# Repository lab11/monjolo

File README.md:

Monjolo
=======

Monjolo sensors are designed to meter energy consumers, such as plug loads,
lighting, water heaters, etc. Monjolo exploits an interesting fact to accomplish
this: energy consuming loads (e.g. overhead lighting) often produce side
channels of energy that can be harvested (e.g. light with a solar panel).
Monjolo nodes use an energy-harvesting power supply to scavenge energy from
these side channels to power themselves. The sensors then infer information
about the original load based on the rate it is able to harvest. Monjolo nodes
follow a simple principle: the faster the rate of harvesting the greater the
amount of energy consumed by the monitored load.

The operation of a Monjolo node proceeds as follows: the harvester charges
a capacitor to some threshold. Once the threshold is met, the processing
core of the node activates and transmits a packet. The capacitor is then
drained to a lower threshold where the processing core is disabled and
the recharging process recommences. A central receiver collects all of these
packets and calculates the activation rate of the Monjolo node. This rate
is then used to meter the energy consumer.

This differs from traditional sensing because there is no explicit sensor
on the device. The sensing apparatus is entirely composed of the
energy-harvester and the packet receiver. All information is contained in
the rate of activations of the Monjolo node.

We have developed Three instantiations of this metering design. First is
Coilcube, a power meter for AC loads. Second is a light sensor for metering
lighting. And third is a thermoelectric design for metering temperature
differential.

Coilcube
--------

[

](https://raw.github.com/lab11/monjolo/master/media/coilcube_case.jpg)
[

](https://raw.github.com/lab11/monjolo/master/media/coilcube_open.jpg)

Coilcube is an AC power meter that comes in two forms: plug-load and split-core.

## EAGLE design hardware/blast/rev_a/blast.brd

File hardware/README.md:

Hardware (PCBs)
===============

This folder contains hardware for the various Monjolo nodes.

| Board                 | Folder             | Description                                                                |
|-----------------------|--------------------|----------------------------------------------------------------------------|
| Coilcube Power Supply | cc_power_supply    | An AC current transformer based energy-harvesting power supply.            |
| Coilcube              | coilcube           | Plug load AC meter. Contains processing core.                              |
| Gecko Power Supply    | gecko_power_supply | Energy-harvesting power supply for solar cell.                             |
| Impulse               | impulse            | Processing core. Contains, uC, radio, antenna, FRAM, and timing capacitor. |
| sEHnsor               | sEHnsor            | Processing core like Impulse based on the CC2538.                          |

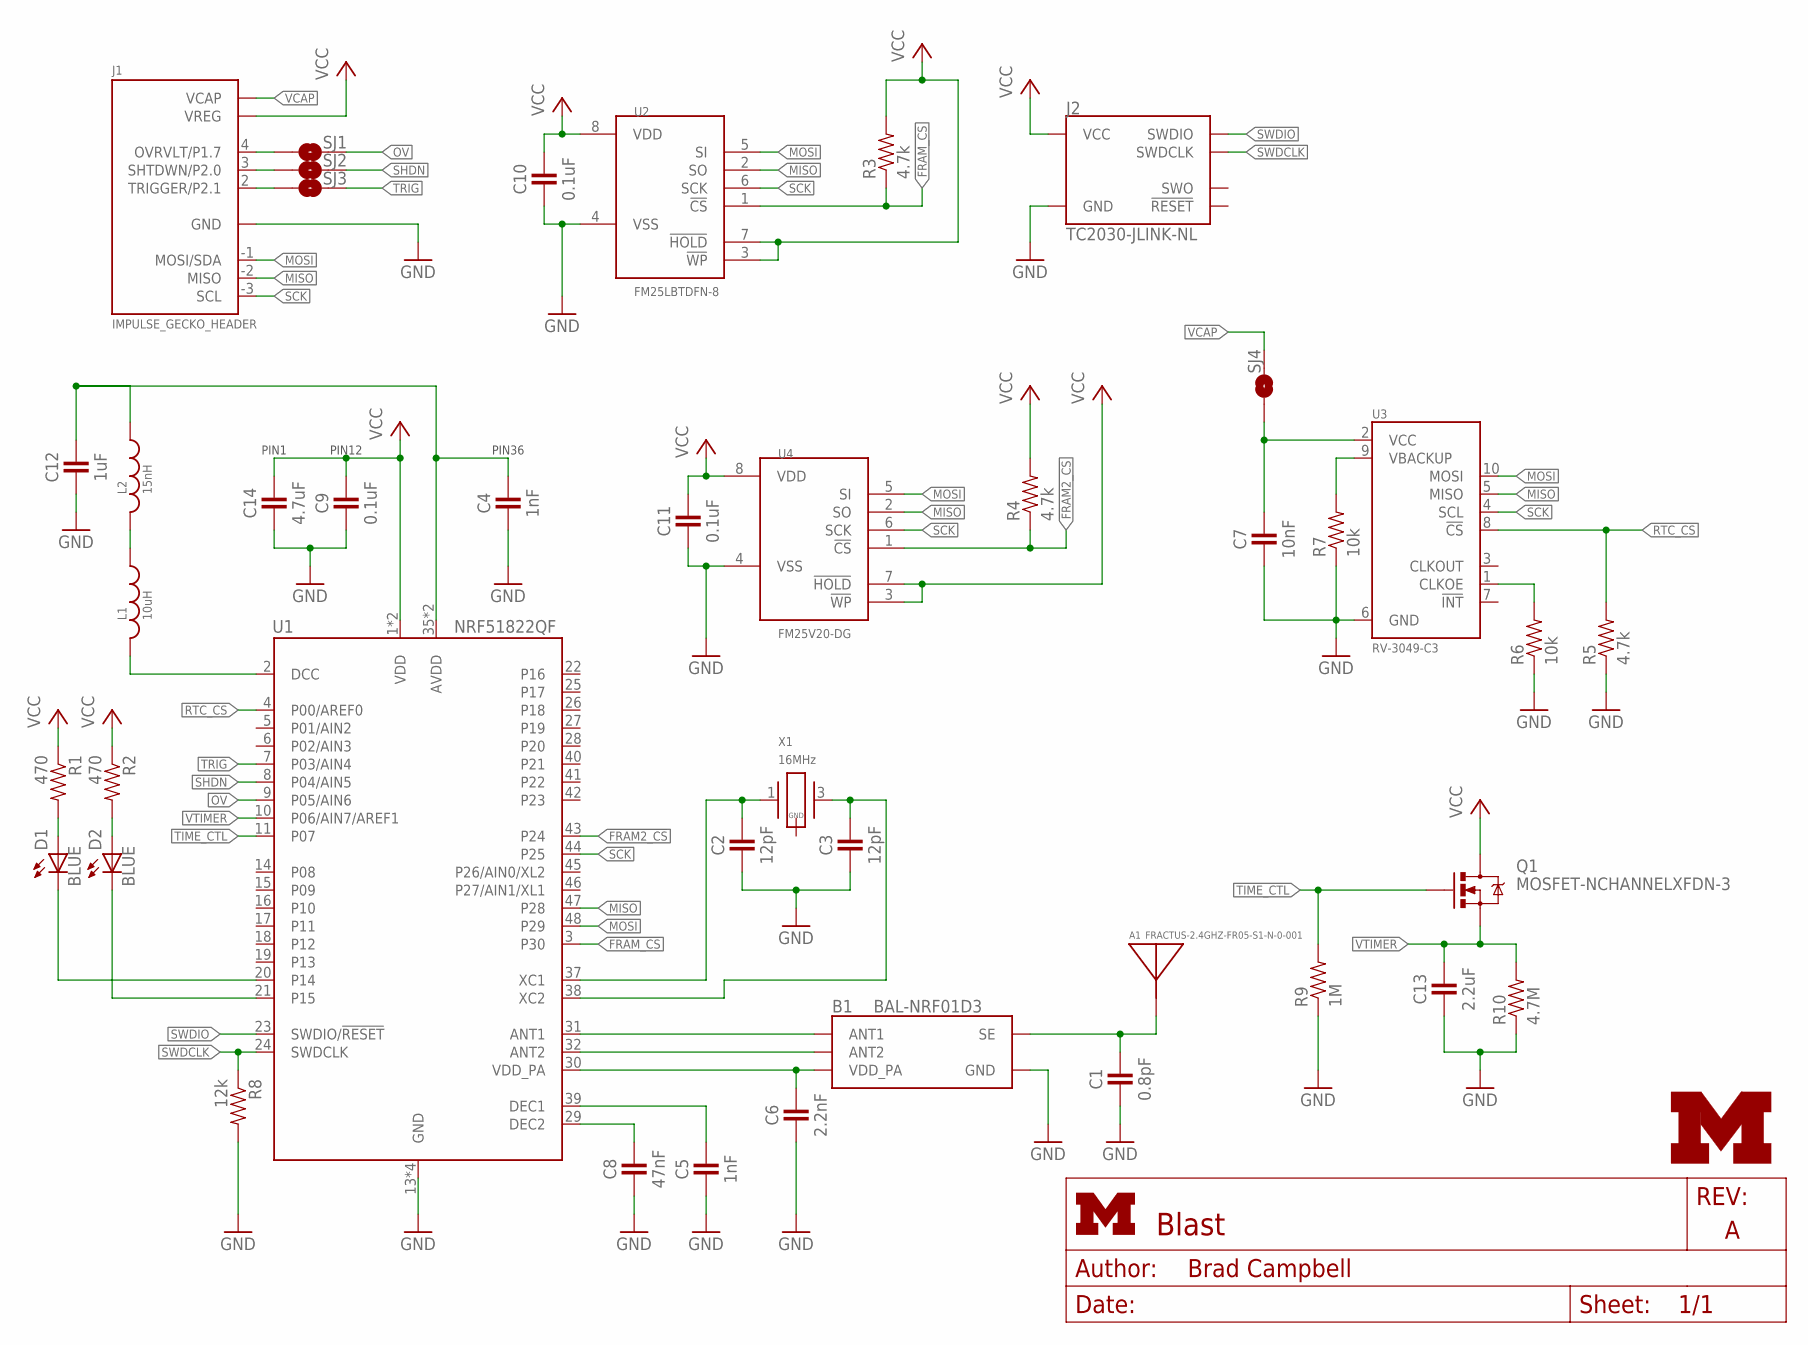
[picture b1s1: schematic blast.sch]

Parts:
A1: FRACTUS-2.4GHZ-FR05-S1-N-0-001; FRACTUS-ANTENNA-FR05-S1-N-0-001
B1: BAL-NRF01D3
C1: 0.8pF; 0402_CAP; DIGIKEY 490-6269-1-ND
C2, C3: 12pF; 0402_CAP; DIGIKEY 490-6197-1-ND
C4, C5: 1nF; 0402_CAP; DIGIKEY 490-1303-1-ND
C6: 2.2nF; 0402_CAP; DIGIKEY 490-5419-1-ND
C7: 10nF; 0402_CAP; DIGIKEY 445-1260-1-ND
C8: 47nF; 0402_CAP; DIGIKEY 445-1264-1-ND
C9, C10, C11: 0.1uF; 0402_CAP; DIGIKEY 445-4952-1-ND
C12: 1uF; 0402_CAP; DIGIKEY 1276-1513-1-ND
C13: 2.2uF; 0402_CAP; DIGIKEY 445-3882-1-ND
C14: 4.7uF; 0402_CAP; DIGIKEY 445-5947-1-ND
D1, D2: BLUE; LED-0603; DIGIKEY 160-1837-1-ND
J1: IMPULSE_GECKO_HEADER; HEADER1X9/0.05IN
J2: TC2030-JLINK-NL; TC2030-IDC-NL
L1: 10uH; 0603_CAP; DIGIKEY 490-4025-1-ND
L2: 15nH; 0402_CAP; DIGIKEY 587-1521-1-ND
Q1: MOSFET-NCHANNELXFDN-3; XFDFN-3
R1, R2: 470; 0402_RES; DIGIKEY RHM470CECT-ND
R3, R4, R5: 4.7k; 0402_RES; DIGIKEY RHM4.7KCECT-ND
R6, R7: 10k; 0402_RES; DIGIKEY RHM10KCECT-ND
R8: 12k; 0402_RES; DIGIKEY RHM12.0KCDCT-ND
R9: 1M; 0402_RES; DIGIKEY RHM1.0MCECT-ND
R10: 4.7M; 0402_RES; DIGIKEY 541-4.7MJCT-ND
SJ1, SJ2, SJ3, SJ4: SOLDERJUMPERNO; SJ_2S-NO
U1: NRF51822QF; QFN-48-6MM; DIGIKEY 1490-1042-1-ND
U2: FM25LBTDFN-8; TDFN-8@1; DIGIKEY FM25L04B-DGRA-ND
U3: RV-3049-C3; MICRO-CRYSTAL-C3
U4: FM25V20-DG; TDFN-8/6MM
U$1: UMICH_SOLID_SMALL; UMICH_SOLID_75MIL
X1: 16MHz; TXC-8Y; DIGIKEY 887-2003-1-ND

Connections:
!FRAM2_CS: R4.1, U1.43 (P24), U4.1 (!CS)
!FRAM_CS: R3.1, U1.3 (P30), U2.1 (!CS)
BATTERY: C7.1, SJ4.1, U3.2 (VCC)
GND: B1.GND, C1.2, C2.2, C3.2, C4.2, C5.2, C6.2, C7.2, C8.2, C9.2, C10.2, C11.2, C12.2, C13.2, C14.2, J1.0 (GND), J2.5 (GND), R5.1, R6.1, R7.1, R8.2, R9.1, R10.1, U1.13 (GND), U1.33 (GND), U1.34 (GND), U1.GND, U2.4 (VSS), U3.6 (GND), U4.4 (VSS)
MISO: J1.-2 (MISO), U1.47 (P28), U2.2 (SO), U3.5 (MISO), U4.2 (SO)
MOSI: J1.-1 (MOSI/SDA), U1.48 (P29), U2.5 (SI), U3.10 (MOSI), U4.5 (SI)
unnamed: D2.C, U1.21 (P15)
unnamed: B1.ANT1, U1.31 (ANT1)
unnamed: B1.ANT2, U1.32 (ANT2)
unnamed: D1.C, U1.20 (P14)
unnamed: R7.2, U3.9 (VBACKUP)
unnamed: R6.2, U3.1 (CLKOE)
unnamed: A1.1, B1.SE, C1.1
unnamed: C4.1, C12.1, L2.1, U1.35 (AVDD), U1.36 (AVDD)
unnamed: L1.2, U1.2 (DCC)
unnamed: L1.1, L2.2
unnamed: D2.A, R2.2
unnamed: C2.1, U1.37 (XC1), X1.1
unnamed: C3.1, U1.38 (XC2), X1.3 (2)
unnamed: C5.1, U1.39 (DEC1)
unnamed: C8.1, U1.29 (DEC2)
unnamed: J1.2 (TRIGGER/P2.1), SJ3.1
unnamed: J1.3 (SHTDWN/P2.0), SJ2.1
unnamed: J1.4 (OVRVLT/P1.7), SJ1.1
unnamed: D1.A, R1.2
OV: SJ1.2, U1.9 (P05/AIN6)
RTC_CS: R5.2, U1.4 (P00/AREF0), U3.8 (!CS)
SCK: J1.-3 (SCL), U1.44 (P25), U2.6 (SCK), U3.4 (SCL), U4.6 (SCK)
SHDN: SJ2.2, U1.8 (P04/AIN5)
SWDCLK: J2.4 (SWDCLK), R8.1, U1.24 (SWDCLK)
SWDIO: J2.2 (SWDIO), U1.23 (SWDIO/!RESET)
TIME_CTL: Q1.G, R9.2, U1.11 (P07)
TRIG: SJ3.2, U1.7 (P03/AIN4)
VCAP: J1.5 (VCAP), SJ4.2
VCC: C9.1, C10.1, C11.1, C14.1, J1.1 (VREG), J2.1 (VCC), Q1.D, R1.1, R2.1, R3.2, R4.2, U1.1 (VDD), U1.12 (VDD), U2.3 (!WP), U2.7 (!HOLD), U2.8 (VDD), U4.3 (!WP), U4.7 (!HOLD), U4.8 (VDD)
VDD_PA: B1.VCC (VDD_PA), C6.1, U1.30 (VDD_PA)
VTIMER: C13.1, Q1.S, R10.2, U1.10 (P06/AIN7/AREF1)

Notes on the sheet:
PIN12
PIN1
PIN36

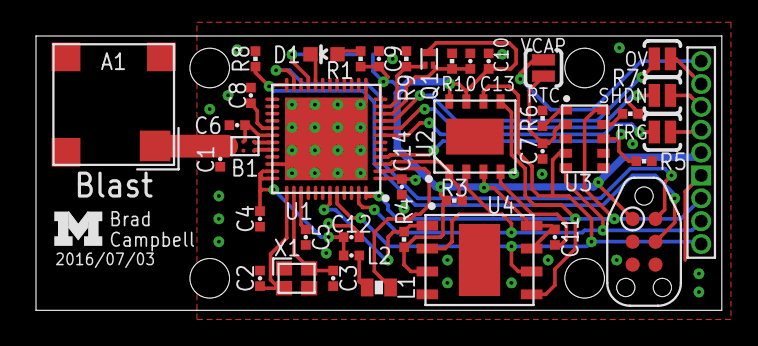
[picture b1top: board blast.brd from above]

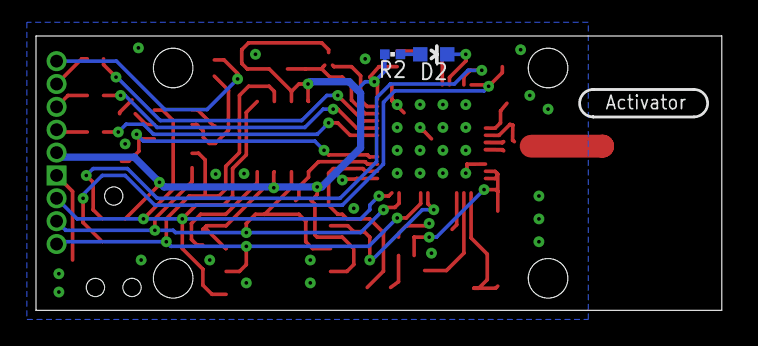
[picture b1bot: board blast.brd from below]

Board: 2 copper layers, 38.1 x 15.2 mm, 43 parts (2 on the bottom side), 37 nets.

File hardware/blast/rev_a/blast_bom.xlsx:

Note | Qty | Value | Device | Package | Parts | Description | DIGIKEY | MOUSER | NEWARK | RICHARDSON_RFPD
 | 1 | FRACTUS-2.4GHZ-FR05-S1-N-0-001 | FRACTUS-2.4GHZ-FR05-S1-N-0-001 | FRACTUS-ANTENNA-FR05-S1-N-0-001 | A1 | Fractus Reach Xtend |  |  |  | FR05-S1-N-0001B
 | 1 | BAL-NRF01D3 | BAL-NRF01D3 | BAL-NRF01D3 | B1 | 50 ohm nominal input / conjugate match balun to nRF51422-QFAA, | 497-13637-1-ND | 511-BAL-NRF01D3
 | 1 | 0.8pF | CAPACITOR | 0402_CAP | C1 | 0402 Capacitor | 490-6269-1-ND
 | 1 | 1uF | CAPACITOR | 0402_CAP | C12 | 0402 Capacitor | 1276-1513-1-ND
 | 1 | 2.2uF | CAPACITOR | 0402_CAP | C13 | 0402 Capacitor | 445-3882-1-ND
 | 1 | 4.7uF | CAPACITOR | 0402_CAP | C14 | 0402 Capacitor | 445-5947-1-ND
 | 2 | 12pF | CAPACITOR | 0402_CAP | C2, C3 | 0402 Capacitor | 490-6197-1-ND
 | 2 | 1nF | CAPACITOR | 0402_CAP | C4, C5 | 0402 Capacitor | 490-1303-1-ND
 | 1 | 2.2nF | CAPACITOR | 0402_CAP | C6 | 0402 Capacitor | 490-5419-1-ND
DNP | 1 | 10nF | CAPACITOR | 0402_CAP | C7 | 0402 Capacitor | 445-1260-1-ND
 | 1 | 47nF | CAPACITOR | 0402_CAP | C8 | 0402 Capacitor | 445-1264-1-ND
 | 2 | 0.1uF | CAPACITOR | 0402_CAP | C9, C10 | 0402 Capacitor | 445-4952-1-ND
DNP | 1 | 0.1uF | CAPACITOR | 0402_CAP | C11 | 0402 Capacitor | 445-4952-1-ND
 | 2 | BLUE | LED0603 | LED-0603 | D1, D2 | LEDs | 160-1837-1-ND
 | 1 | IMPULSE_GECKO_HEADER | IMPULSE_GECKO_HEADER | HEADER1X9/0.05IN | J1 | Header on the impulse EPIC-esque board.
 | 1 | TC2030-JLINK-NL | TC2030-JLINK-NL | TC2030-IDC-NL | J2
 | 1 | 10uH | INDUCTOR0603 | 0603_CAP | L1 |  | 490-4025-1-ND
 | 1 | 15nH | INDUCTOR0402 | 0402_CAP | L2 |  | 587-1521-1-ND
 | 1 | MOSFET-NCHANNELXFDN-3 | MOSFET-NCHANNELXFDN-3 | XFDFN-3 | Q1 | Generic NMOS footprint | DMN2400UFB4-7DICT-ND
 | 2 | 470 | RESISTOR | 0402_RES | R1, R2 | Resistor | RHM470CECT-ND
 | 1 | 4.7M | RESISTOR | 0402_RES | R10 | Resistor | 541-4.7MJCT-ND
 | 1 | 4.7k | RESISTOR | 0402_RES | R3 | Resistor | RHM4.7KCECT-ND
DNP | 2 | 4.7k | RESISTOR | 0402_RES | R4, R5 | Resistor | RHM4.7KCECT-ND
DNP | 2 | 10k | RESISTOR | 0402_RES | R6, R7 | Resistor | RHM10KCECT-ND
 | 1 | 12k | RESISTOR | 0402_RES | R8 | Resistor | RHM12.0KCDCT-ND
 | 1 | 1M | RESISTOR | 0402_RES | R9 | Resistor | RHM1.0MCECT-ND
 | 1 | NRF51822QF | NRF51822QF | QFN-48-6MM | U1 | Multiprotocol Bluetooth® 4.0 low energy/2.4 GHz RF SoC | 1490-1042-1-ND | 949-NRF51822-QFAC-R7
 | 1 | FM25LBTDFN-8 | FM25LBTDFN-8 | TDFN-8@1 | U2 | IC FRAM 4KBIT 10MHZ 8SOIC | FM25L04B-DGRA-ND | 877-FM25L04B-DG
DNP | 1 | RV-3049-C3 | RV-3049-C3 | MICRO-CRYSTAL-C3 | U3 | The RV-3049-C3 is an ultra miniature Real-Time-Clock Module |  |  | RV-3049-C3
DNP | 1 | FM25V20-DG | FM25V20-DG | TDFN-8/6MM | U4 | Cypress FRAM | FM25V20-DGRA-ND | 877-FM25V20-DG
 | 1 | 16MHz | TXC-8Y | TXC-8Y | X1 | 2mmx1.6mm SMD Crystal | 887-2003-1-ND

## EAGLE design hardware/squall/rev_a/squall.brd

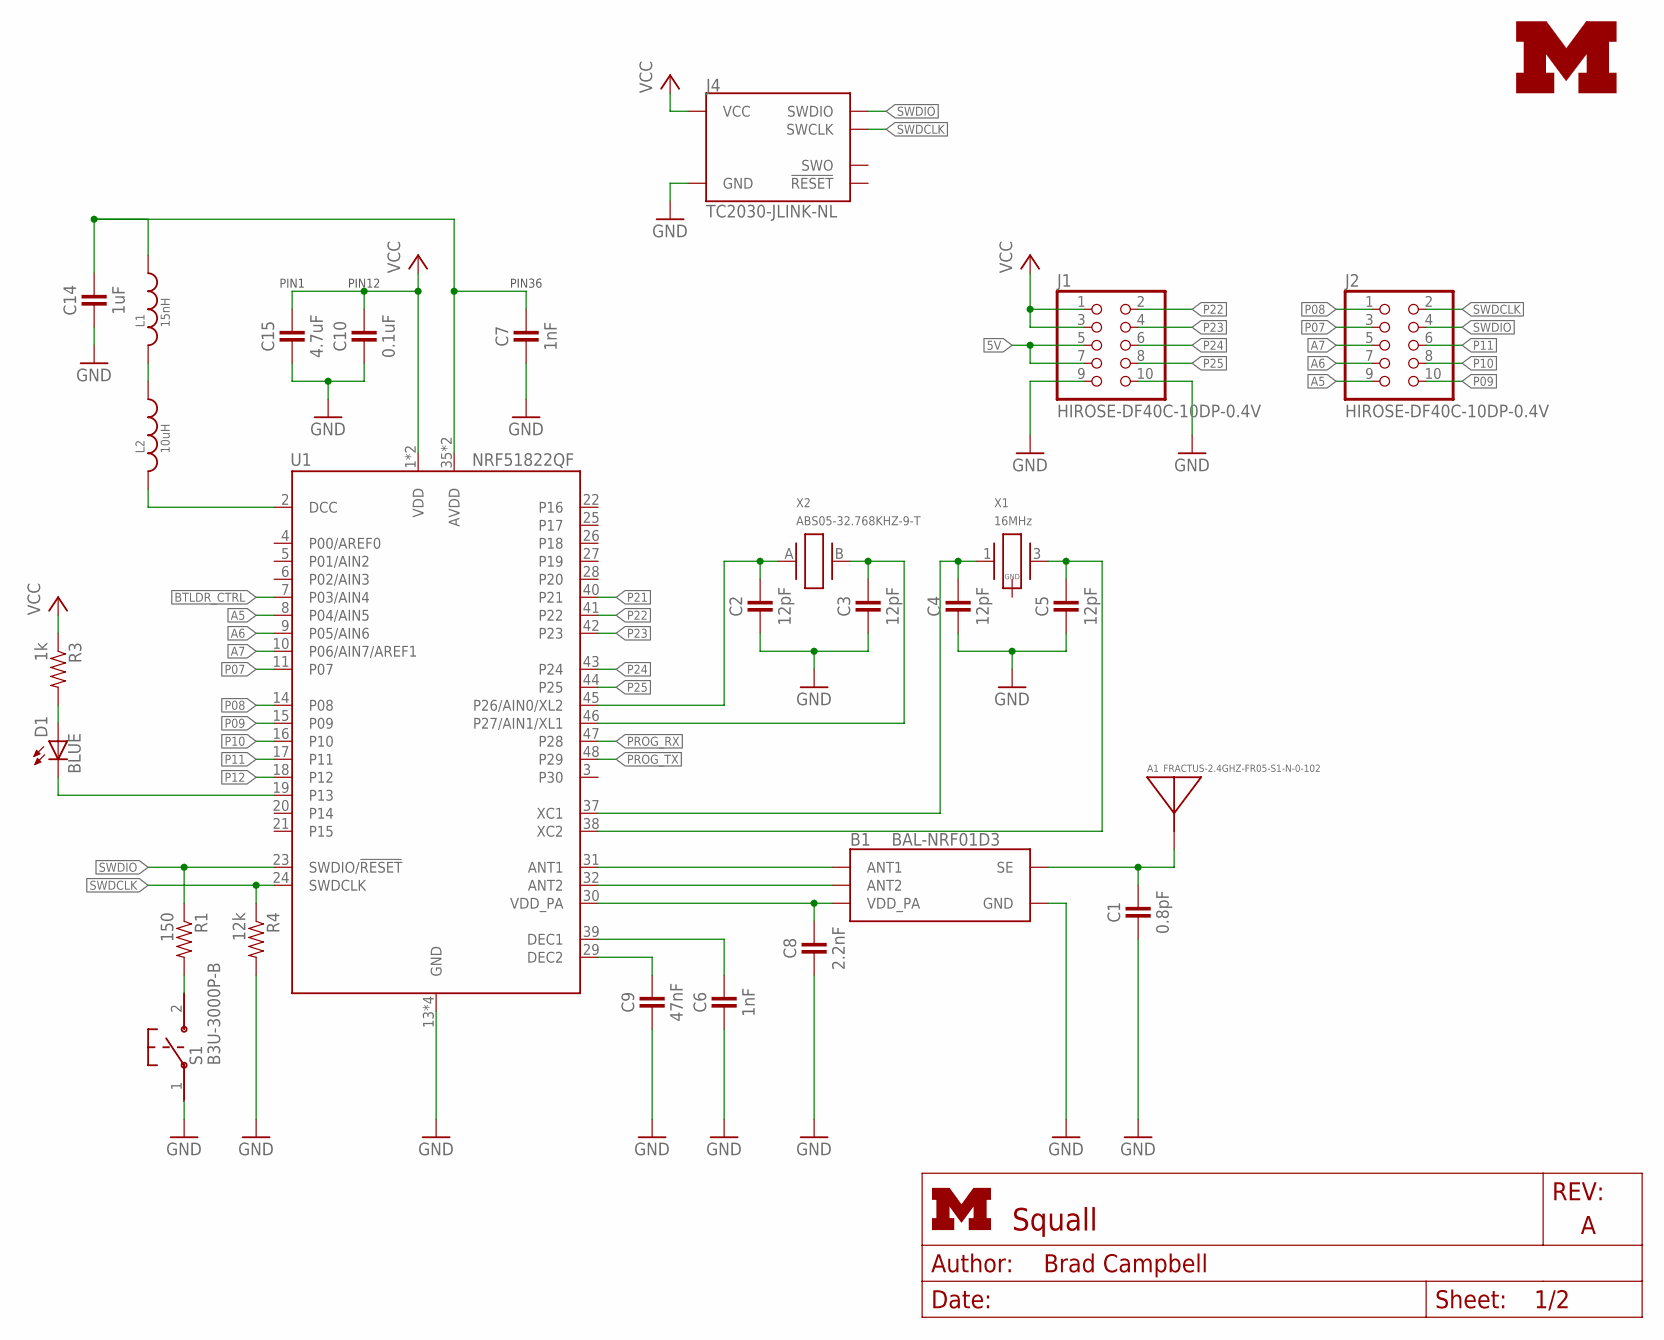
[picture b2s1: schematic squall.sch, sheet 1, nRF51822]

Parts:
A1: FRACTUS-2.4GHZ-FR05-S1-N-0-102; FRACTUS-ANTENNA-FR05-S1-N-0-102
B1: BAL-NRF01D3
C1: 0.8pF; 0402_CAP; DIGIKEY 490-5419-1-ND
C2, C3, C4, C5: 12pF; 0402_CAP; DIGIKEY 490-6197-1-ND
C6, C7: 1nF; 0402_CAP; DIGIKEY 490-1303-1-ND
C8: 2.2nF; 0402_CAP; DIGIKEY 490-5419-1-ND
C9: 47nF; 0402_CAP; DIGIKEY 445-1264-1-ND
C10: 0.1uF; 0402_CAP; DIGIKEY 445-4952-1-ND
C14: 1uF; 0402_CAP; DIGIKEY 1276-1513-1-ND
C15: 4.7uF; 0402_CAP; DIGIKEY 445-5947-1-ND
D1: BLUE; LED-0603
J1, J2: HIROSE-DF40C-10DP-0.4V; 2X5/SMD/0.4MM
J4: TC2030-JLINK-NL; TC2030-IDC-NL
L1: 15nH; 0402_CAP; DIGIKEY 587-1521-1-ND
L2: 10uH; 0603_CAP; DIGIKEY 490-4025-1-ND
LOGO1: UMICH_SOLID_TINY; UMICH_SOLID_50MIL
R1: 150; 0402_RES; DIGIKEY RHM150CDCT-ND
R3: 1k; 0402_RES; DIGIKEY RHM1.0KCECT-ND
R4: 12k; 0402_RES; DIGIKEY RHM12.0KCDCT-ND
S1: B3U-3000P-B
U1: NRF51822QF; QFN-48-6MM
X1: 16MHz; TXC-8Y; DIGIKEY 887-2003-1-ND
X2: ABS05-32.768KHZ-9-T; ABS05

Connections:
5V: J1.5, J1.7; also elsewhere on the board
A0: C2.1, U1.45 (P26/AIN0/XL2), X2.A (1)
A1: C3.1, U1.46 (P27/AIN1/XL1), X2.B (2)
A5: J2.9, U1.8 (P04/AIN5)
A6: J2.7, U1.9 (P05/AIN6)
A7: J2.5, U1.10 (P06/AIN7/AREF1)
AVDD: C7.1, C14.1, L1.1, U1.35 (AVDD), U1.36 (AVDD)
BTLDR_CTRL: U1.7 (P03/AIN4); also elsewhere on the board
DCC: L2.2, U1.2 (DCC)
GND: B1.GND, C1.2, C2.2, C3.2, C4.2, C5.2, C6.2, C7.2, C8.2, C9.2, C10.2, C14.2, C15.2, J1.9, J1.10, J4.5 (GND), R4.2, S1.1, U1.13 (GND), U1.33 (GND), U1.34 (GND), U1.GND; also elsewhere on the board
unnamed: B1.ANT1, U1.31 (ANT1)
unnamed: B1.ANT2, U1.32 (ANT2)
unnamed: D1.C, U1.19 (P13)
unnamed: R1.2, S1.2
unnamed: A1.1, B1.SE, C1.1
unnamed: L1.2, L2.1
unnamed: C4.1, U1.37 (XC1), X1.1
unnamed: C5.1, U1.38 (XC2), X1.3 (2)
unnamed: C6.1, U1.39 (DEC1)
unnamed: C9.1, U1.29 (DEC2)
unnamed: D1.A, R3.2
P07: J2.3, U1.11 (P07)
P08: J2.1, U1.14 (P08)
P09: J2.10, U1.15 (P09)
P10: J2.8, U1.16 (P10)
P11: J2.6, U1.17 (P11)
P12: U1.18 (P12)
P21: U1.40 (P21)
P22: J1.2, U1.41 (P22)
P23: J1.4, U1.42 (P23)
P24: J1.6, U1.43 (P24)
P25: J1.8, U1.44 (P25)
PROG_RX: U1.47 (P28); also elsewhere on the board
PROG_TX: U1.48 (P29); also elsewhere on the board
SWDCLK: J2.2, J4.4 (SWCLK), R4.1, U1.24 (SWDCLK)
SWDIO: J2.4, J4.2 (SWDIO), R1.1, U1.23 (SWDIO/!RESET)
VCC: C10.1, C15.1, J1.1, J1.3, J4.1 (VCC), R3.1, U1.1 (VDD), U1.12 (VDD); also elsewhere on the board
VDD_PA: B1.VCC (VDD_PA), C8.1, U1.30 (VDD_PA)

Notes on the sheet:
PIN12
PIN1
PIN36

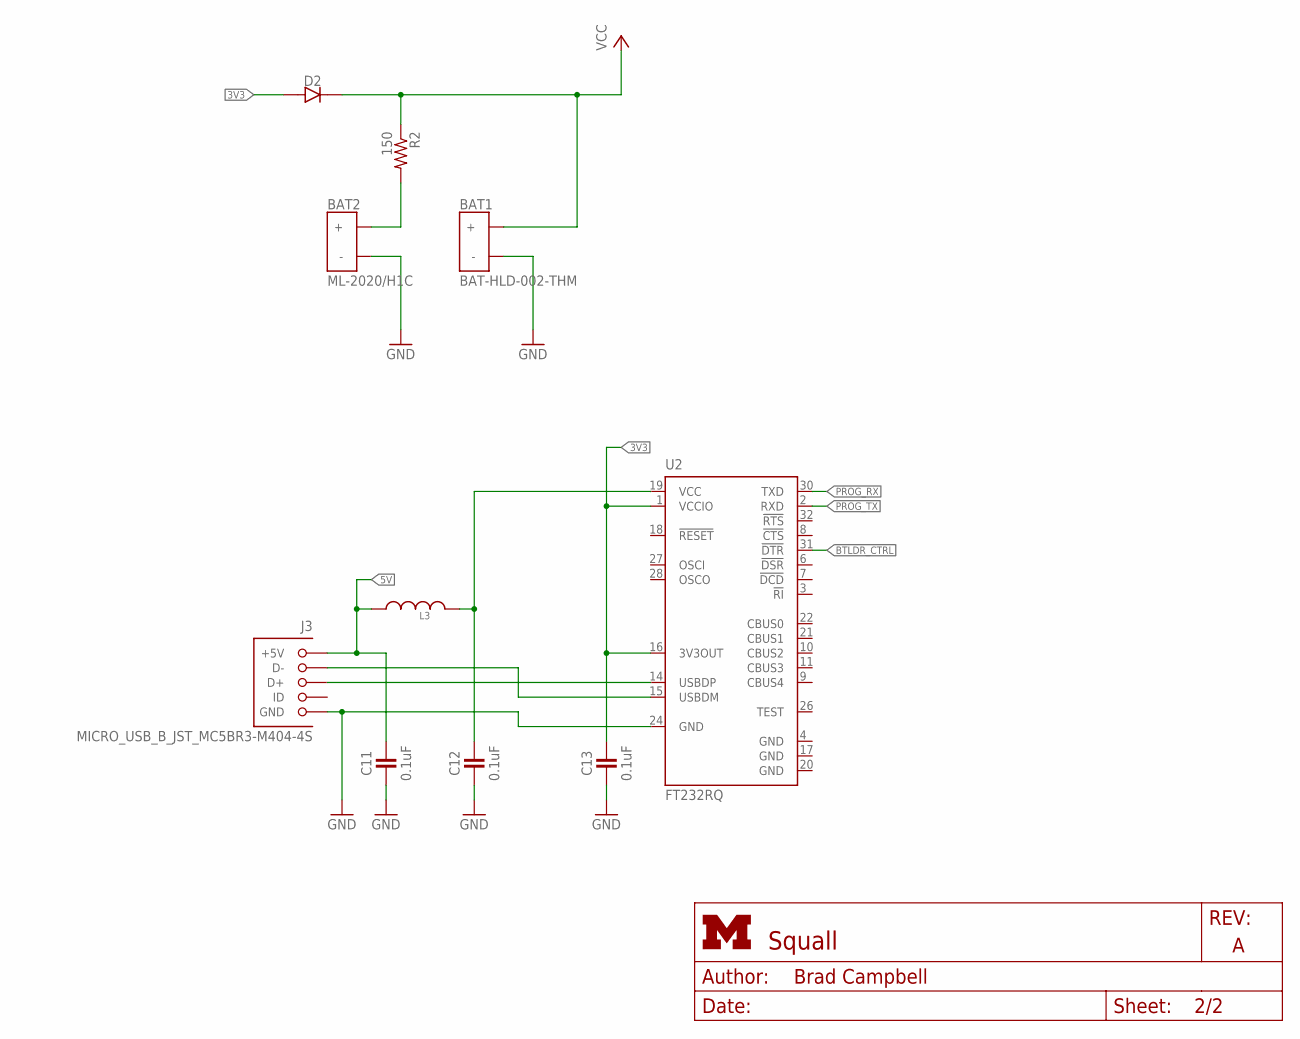
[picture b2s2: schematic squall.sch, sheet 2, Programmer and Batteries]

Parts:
BAT1: BAT-HLD-002-THM
BAT2: ML-2020/H1C
C11, C12, C13: 0.1uF; 0402_CAP; DIGIKEY 490-1318-6-ND
D2: DIODE; 0402_DIODE; DIGIKEY 641-1271-1-ND
J3: MICRO_USB_B_JST_MC5BR3-M404-4S; USB_MICRO_B-JST-MC5BR3-M404-4S-TB
L3: INDUCTOR0402; 0402_CAP; DIGIKEY 445-2979-1-ND
R2: 150; 0402_RES; DIGIKEY RHM150CDCT-ND
U2: FT232RQ; QFN32

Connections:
3V3: C13.1, D2.ANODE, U2.1 (VCCIO), U2.16 (3V3OUT)
5V: C11.1, J3.1 (+5V), L3.1; also elsewhere on the board
BTLDR_CTRL: U2.31 (!DTR); also elsewhere on the board
FTDI_VCC: C12.1, L3.2, U2.19 (VCC)
GND: BAT1.GND (-), BAT2.NEG (-), C11.2, C12.2, C13.2, J3.5 (GND), U2.4 (GND), U2.17 (GND), U2.20 (GND), U2.24 (GND); also elsewhere on the board
unnamed: BAT2.POS (+), R2.2
unnamed: J3.3 (D+), U2.14 (USBDP)
unnamed: J3.2 (D-), U2.15 (USBDM)
PROG_RX: U2.30 (TXD); also elsewhere on the board
PROG_TX: U2.2 (RXD); also elsewhere on the board
VCC: BAT1.POS1 (+), BAT1.POS2 (+), BAT1.POS3 (+), BAT1.POS4 (+), D2.CATHODE, R2.1; also elsewhere on the board

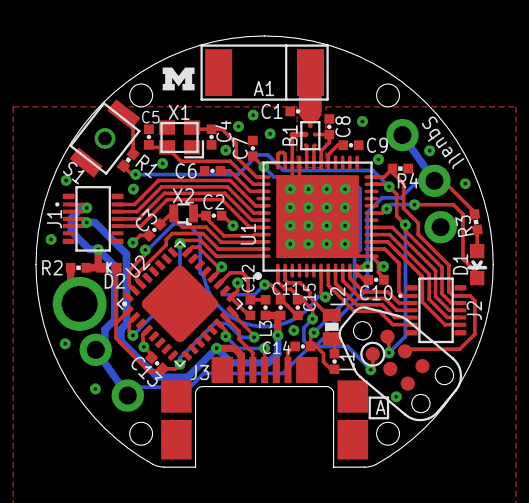
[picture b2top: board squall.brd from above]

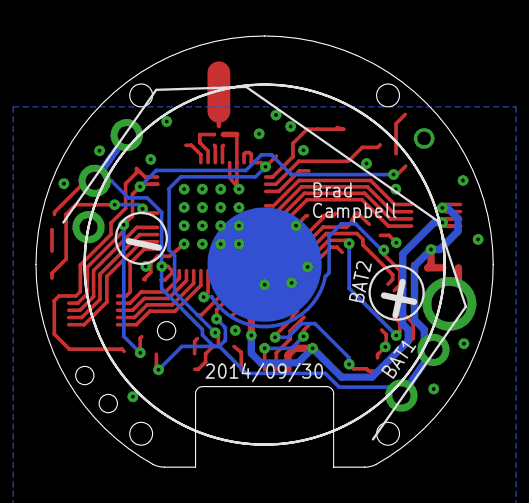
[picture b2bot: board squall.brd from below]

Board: 2 copper layers, 25.4 x 24.0 mm, 38 parts (2 on the bottom side), 41 nets.

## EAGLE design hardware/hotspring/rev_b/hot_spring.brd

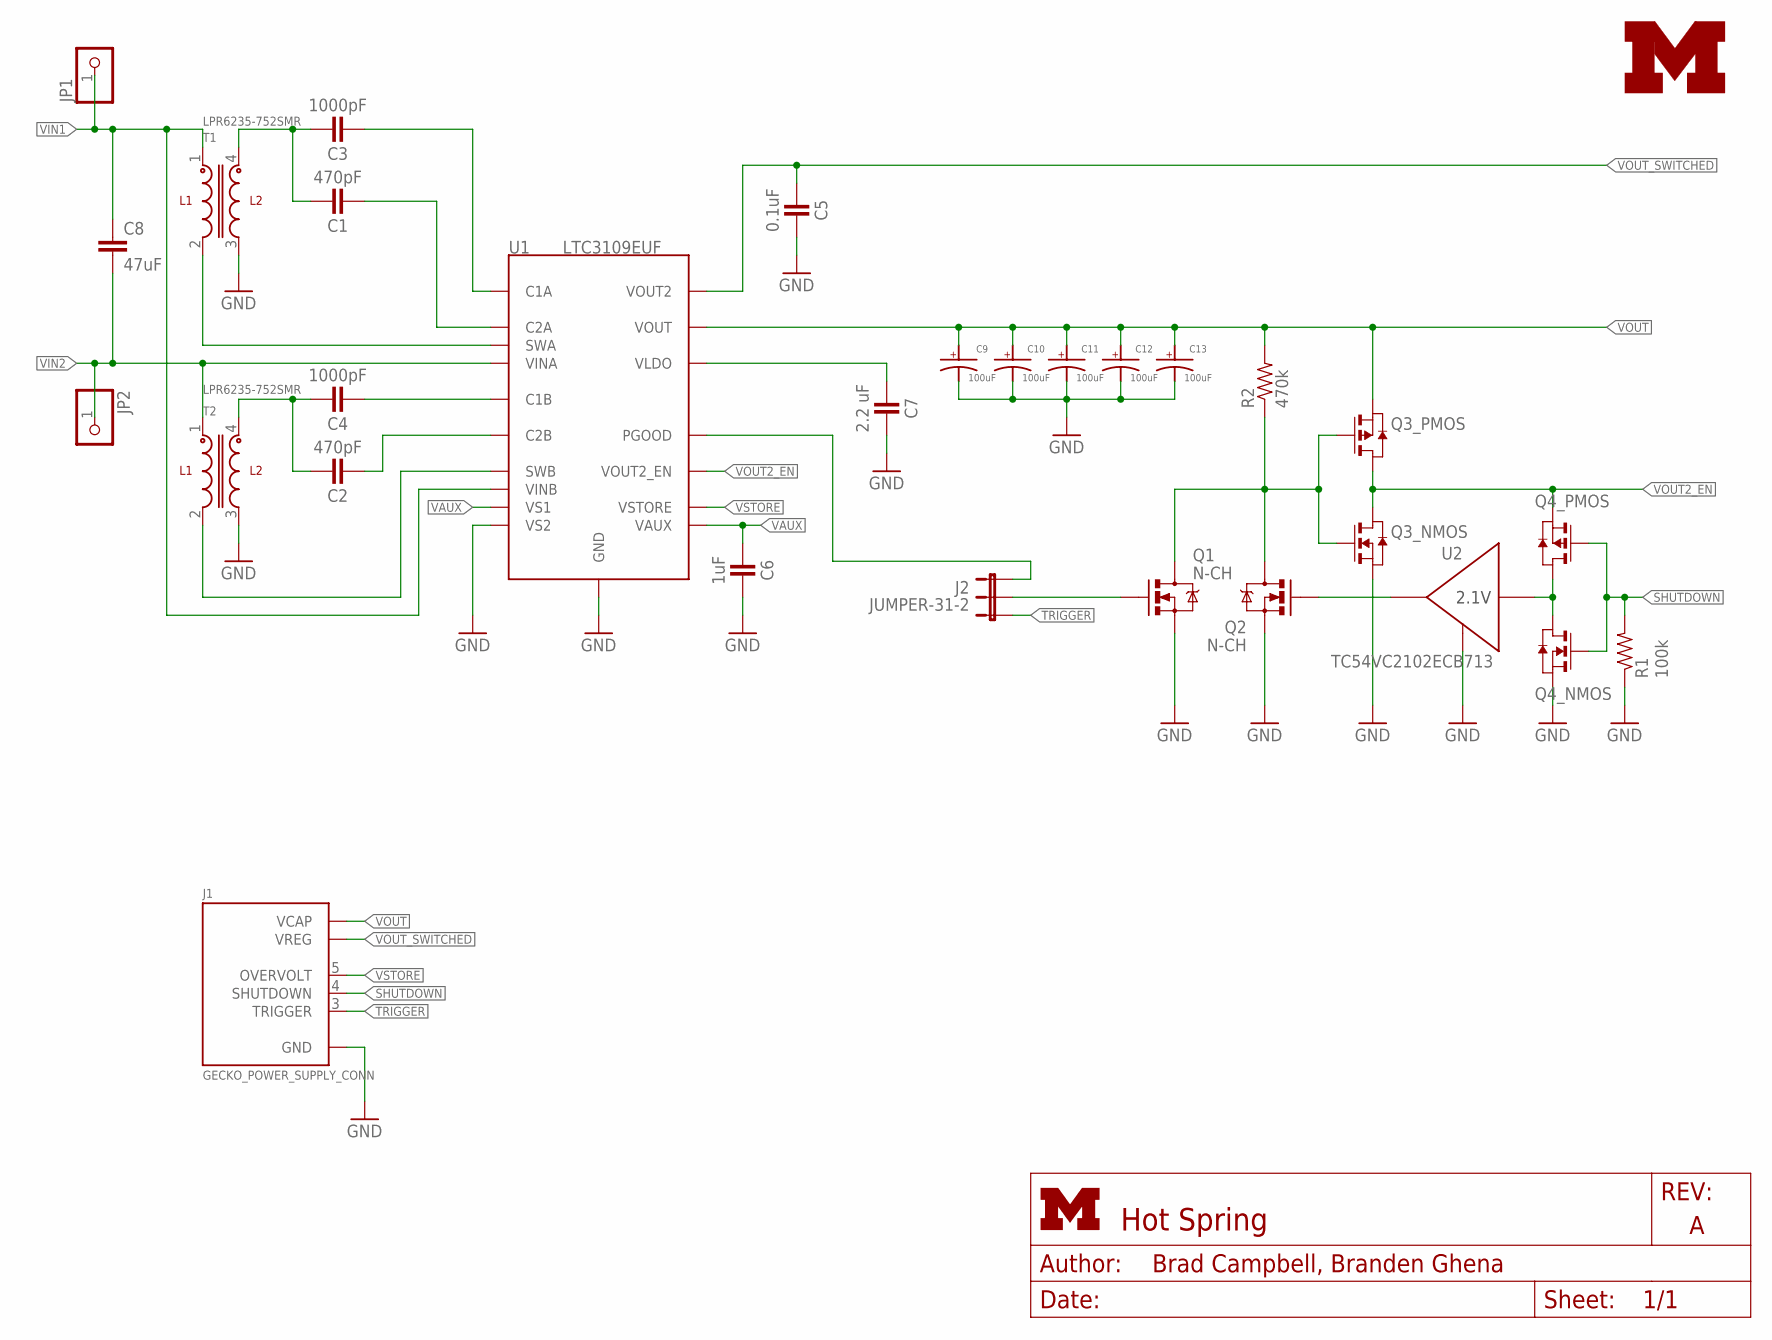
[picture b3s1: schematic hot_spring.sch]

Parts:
C1, C2: 470pF; 0402_CAP; DIGIKEY 445-1255-1-ND
C3, C4: 1000pF; 0402_CAP; DIGIKEY 445-1256-1-ND
C5: 0.1uF; 0402_CAP; DIGIKEY 445-4952-1-ND
C6: 1uF; 0402_CAP; DIGIKEY 445-13185-1-ND
C7: 2.2 uF; 0402_CAP; DIGIKEY 445-4999-1-ND
C8: 47uF; 1210; DIGIKEY 399-5515-1-ND
C9, C10, C11, C12, C13: 100uF; CAP1210; DIGIKEY 478-3130-1-ND
J1: GECKO_POWER_SUPPLY_CONN; HEADER1X6/0.05IN
J2: JUMPER-31-2; SJ_3_PASTE1&2
JP1, JP2: PINHD-1X1; 1X01
LOGO1: UMICH_SOLID_SMALL; UMICH_SOLID_75MIL
Q1, Q2: MOSFET-NCHANNELSMD; SOT23-3; DIGIKEY FDV301NCT-ND
Q3, Q4: DUAL_MOSFET_NP; TSOP-6
R1: 100k; 0402_RES; DIGIKEY RHM100KCDCT-ND
R2: 470k; 0402_RES; DIGIKEY RHM470KCDCT-ND
T1, T2: LPR6235-752SMR; LPR6235
U1: LTC3109EUF; QFN-20-4MM
U2: TC54VC2102ECB713; SOT-23

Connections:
GND: C5.1, C6.1, C7.1, C9.ANODE, C10.ANODE, C11.ANODE, C12.ANODE, C13.ANODE, J1.1 (GND), Q1.2 (S), Q2.2 (S), Q3.5 (S), Q4.5 (S), R1.1, T1.3, T2.3, U1.8 (GND), U1.11 (GND), U1.16 (GND), U1.20 (VS2), U1.GND, U2.2 (GND)
unnamed: C2.1, C4.1, T2.4
unnamed: C1.1, C3.1, T1.4
unnamed: C3.2, U1.18 (C1A)
unnamed: C1.2, U1.17 (C2A)
unnamed: Q4.4 (D), Q4.6 (D), U2.3 (IN)
unnamed: C4.2, U1.9 (C1B)
unnamed: C2.2, U1.10 (C2B)
unnamed: C7.2, U1.7 (VLDO)
unnamed: T1.2, U1.15 (SWA)
unnamed: T2.2, U1.12 (SWB)
unnamed: J2.2, Q1.1 (G)
unnamed: Q2.1 (G), U2.1 (OUT)
unnamed: Q1.3 (D), Q2.3 (D), Q3.1 (G), Q3.3 (G), R2.1
PGOOD: J2.1, U1.6 (PGOOD)
SHUTDOWN: J1.4 (SHUTDOWN), Q4.1 (G), Q4.3 (G), R1.2
TRIGGER: J1.3 (TRIGGER), J2.3
VAUX: C6.2, U1.2 (VAUX), U1.19 (VS1)
VIN1: C8.1, JP1.1, T1.1, U1.13 (VINB)
VIN2: C8.2, JP2.1, T2.1, U1.14 (VINA)
VOUT: C9.CATHODE, C10.CATHODE, C11.CATHODE, C12.CATHODE, C13.CATHODE, J1.6 (VCAP), Q3.2 (S), R2.2, U1.3 (VOUT)
VOUT2_EN: Q3.4 (D), Q3.6 (D), Q4.2 (S), U1.5 (VOUT2_EN)
VOUT_SWITCHED: C5.2, J1.2 (VREG), U1.4 (VOUT2)
VSTORE: J1.5 (OVERVOLT), U1.1 (VSTORE)

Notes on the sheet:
N-CH
2.1V

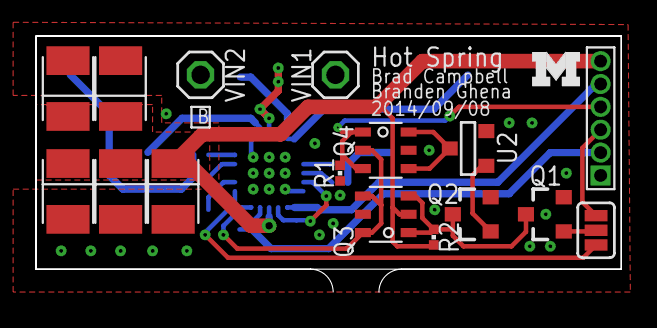
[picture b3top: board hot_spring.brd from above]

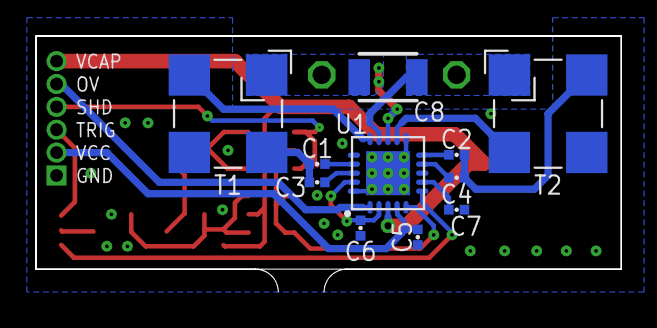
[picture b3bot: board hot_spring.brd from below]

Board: 2 copper layers, 32.5 x 14.2 mm, 28 parts (11 on the bottom side), 24 nets.

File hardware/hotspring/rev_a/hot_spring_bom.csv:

# Bill of Materials
# Converted from hot_spring_bom.xlsx
# Generated by bom_to_text.py

Qty,Value,Device,Package,Parts,Description,COILCRAFT,DIGIKEY,NEWARK
2,470pF,CAPACITOR,0402_CAP,"C1, C2",0402 Capacitor,,445-1255-1-ND,
2,1000pF,CAPACITOR,0402_CAP,"C3, C4",0402 Capacitor,,445-1256-1-ND,
1,0.1uF,CAPACITOR,0402_CAP,C5,0402 Capacitor,,445-4952-1-ND,
1,1uF,CAPACITOR,0402_CAP,C6,0402 Capacitor,,445-13185-1-ND,
1,2.2 uF,CAPACITOR,0402_CAP,C7,0402 Capacitor,,445-4999-1-ND,
1,47uF,CAP1210,1210,C8,Capacitor,,399-5515-1-ND,
5,100uF,1210_CAP_POLARIZED,CAP1210,"C9, C10, C11, C12, C13",Capacitor,,478-3130-1-ND,
2,MOSFET-NCHANNELSMD,MOSFET-NCHANNELSMD,SOT23-3,"Q1, Q2",NMOS,,FDV301NCT-ND,
1,DUAL_MOSFET_NP,DUAL_MOSFET_NP,TSOP-6,Q3,MOSFET N/P-CH 20V 2A 6-TSOP,,SI3585DV-T1-E3CT-ND,
1,250k,RESISTOR0402_RES,0402_RES,R1,Resistor,,RHM249KCDCT-ND,
1,470k,RESISTOR0402_RES,0402_RES,R2,Resistor,,RHM470KCDCT-ND,
1,500k,RESISTOR0402_RES,0402_RES,R3,Resistor,,RHM499KCDCT-ND,
2,LPR6235-752SMR,LPR6235-752SMR,LPR6235,"T1, T2",Transformer 100:1,LPR6235-752SMR,,
1,LTC3109EUF,LTC3109EUF,QFN-20-4MM,U1,IC BOOST CONVERTER PMU 20QFN,,LTC3109EUF#PBF-ND,84R6674

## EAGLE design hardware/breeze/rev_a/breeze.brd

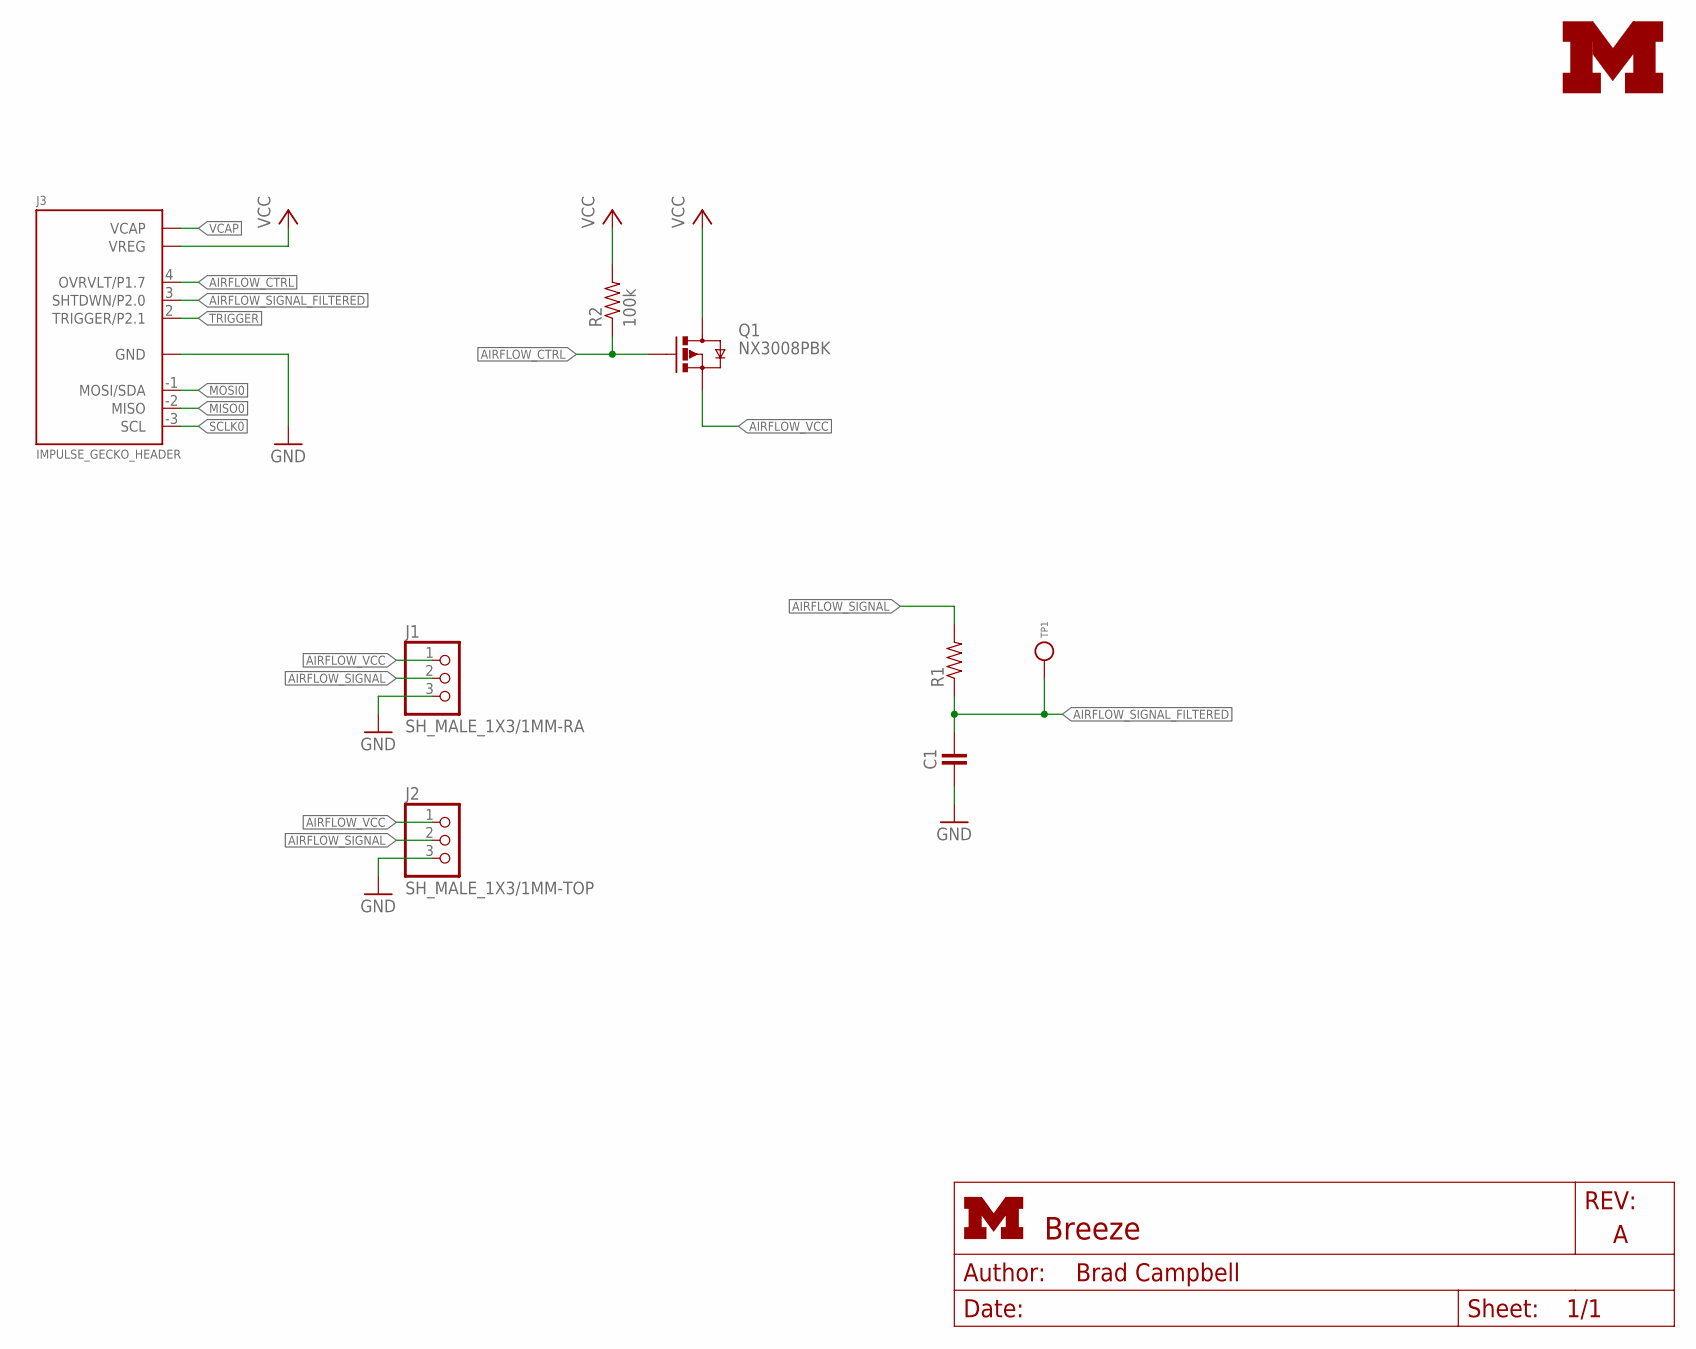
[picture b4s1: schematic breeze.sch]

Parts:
C1: CAPACITOR; 0402_CAP
J1: SH_MALE_1X3/1MM-RA; 1X3/SMD/SH/RA/1MM
J2: SH_MALE_1X3/1MM-TOP; 1X3/SMD/SH/1MM
J3: IMPULSE_GECKO_HEADER; HEADER1X9/0.05IN
LOGO1: UMICH_SOLID_TINY; UMICH_SOLID_50MIL
Q1: NX3008PBK; SOT23-3
R1: RESISTOR0402_RES; 0402_RES
R2: 100k; 0402_RES
TP1: TEST_POINT_0.040IN; TESTPOINT_0.040IN

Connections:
AIRFLOW_CTRL: J3.4 (OVRVLT/P1.7), Q1.1 (G), R2.1
AIRFLOW_SIGNAL: J1.2, J2.2, R1.2
AIRFLOW_SIGNAL_FILTERED: C1.1, J3.3 (SHTDWN/P2.0), R1.1, TP1.TESTPOINT
AIRFLOW_VCC: J1.1, J2.1, Q1.2 (S)
GND: C1.2, J1.3, J2.3, J3.0 (GND)
MISO0: J3.-2 (MISO)
MOSI0: J3.-1 (MOSI/SDA)
SCLK0: J3.-3 (SCL)
TRIGGER: J3.2 (TRIGGER/P2.1)
VCAP: J3.5 (VCAP)
VCC: J3.1 (VREG), Q1.3 (D), R2.2

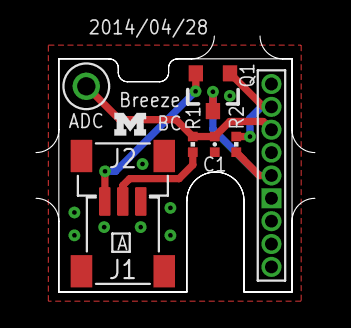
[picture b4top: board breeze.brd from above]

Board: 2 copper layers, 15.5 x 14.2 mm, 9 parts (0 on the bottom side), 6 nets.

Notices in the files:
parts and their libraries:
SparkFun-Passives: Licensing: CC v3.0 Share-Alike You are welcome to use this library for commercial purposes.
